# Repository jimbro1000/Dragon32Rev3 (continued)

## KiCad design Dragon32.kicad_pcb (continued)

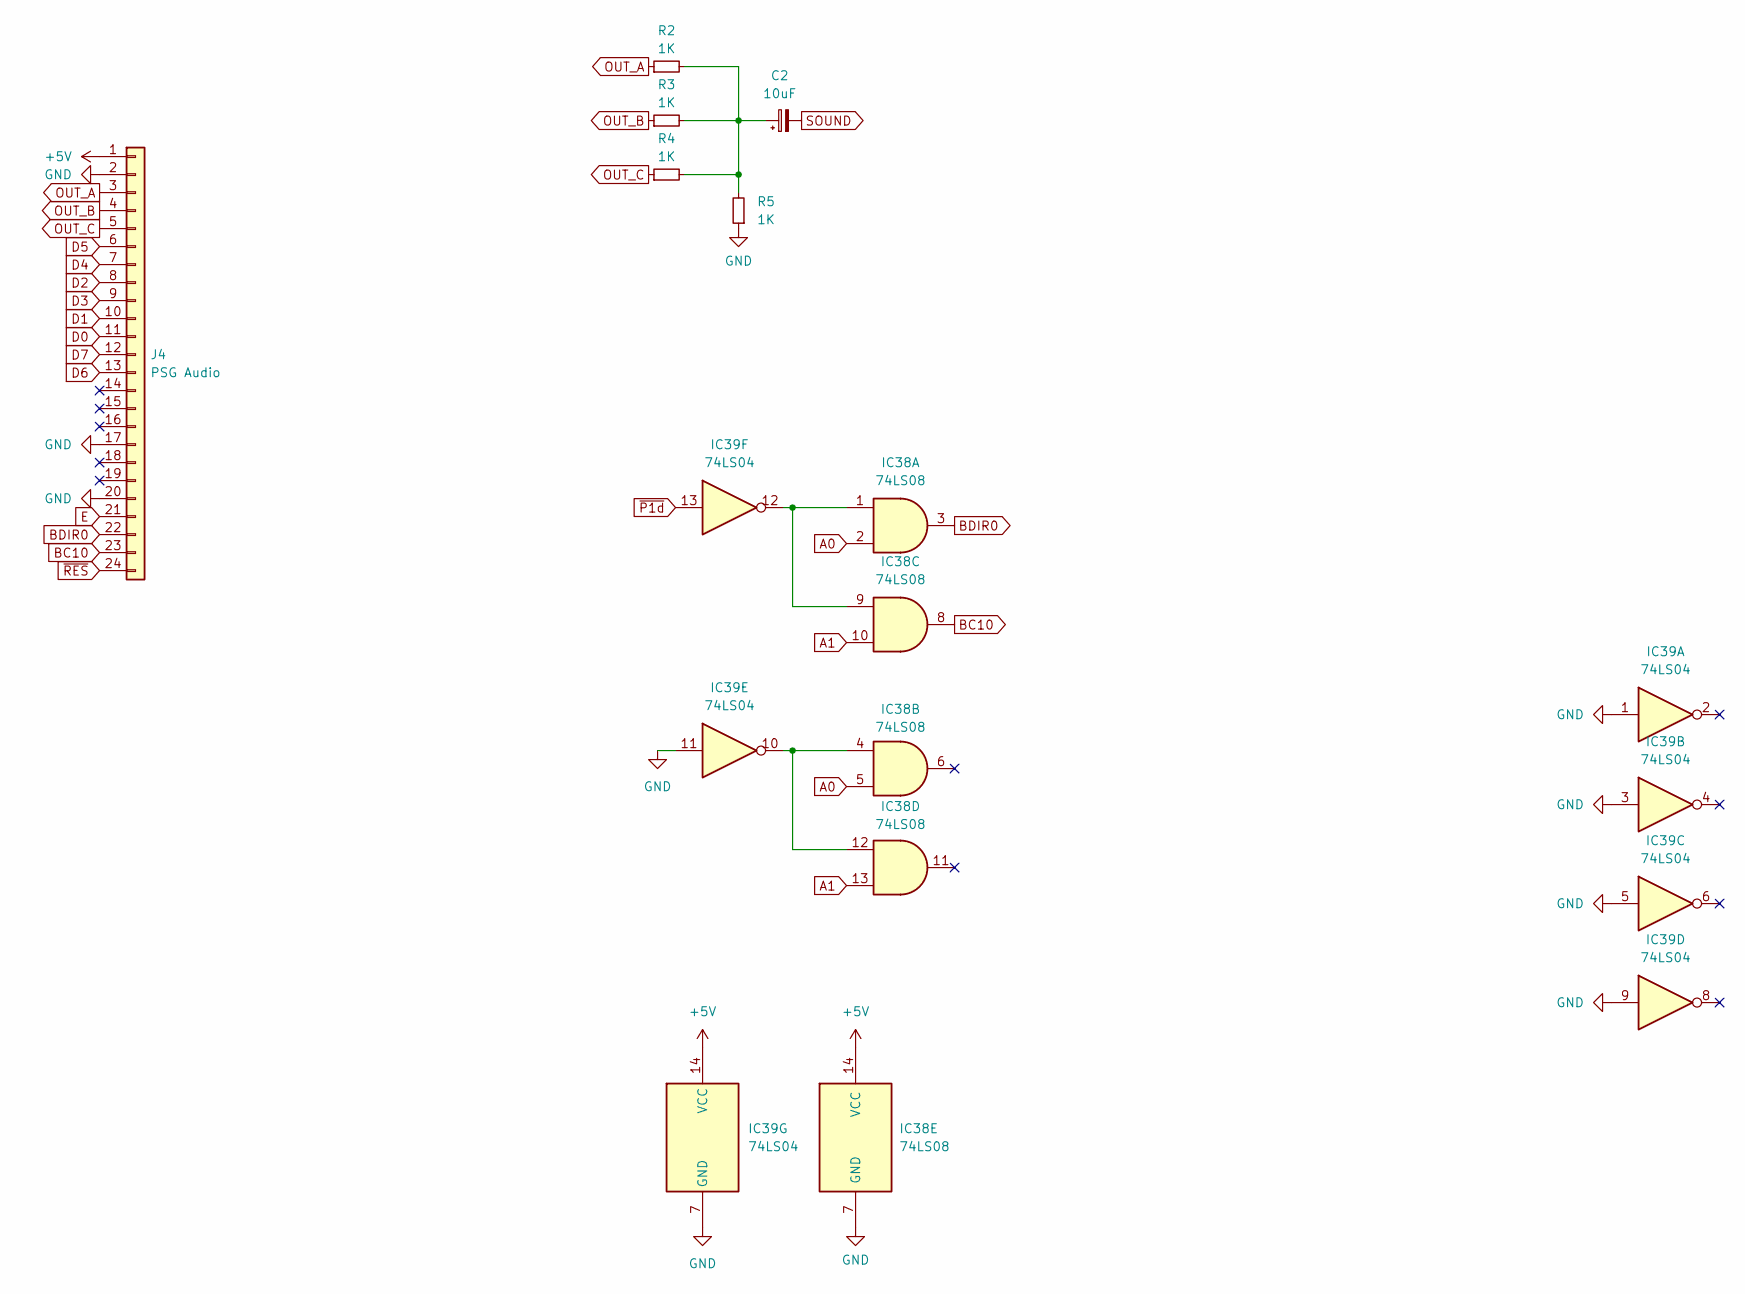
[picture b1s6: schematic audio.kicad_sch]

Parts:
C2: 10uF; CP_Radial_D5.0mm_P2.50mm
IC38: 74LS08; DIP-14_W7.62mm; LCSC C22394768
IC39: 74LS04; DIP-14_W7.62mm; LCSC C22374093
J4: PSG Audio; AY-QTHT
R2, R3, R4: 1K; R_Axial_DIN0207_L6.3mm_D2.5mm_P10.16mm_Horizontal
R5: 1K; R_Axial_DIN0207_L6.3mm_D2.5mm_P2.54mm_Vertical

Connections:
+5V: IC38.14 (VCC), IC39.14 (VCC), J4.1; also elsewhere on the board
A0: IC38.2, IC38.5; also elsewhere on the board
A1: IC38.10, IC38.13; also elsewhere on the board
BC10: IC38.8, J4.23
BDIR0: IC38.3, J4.22
D0: J4.11; also elsewhere on the board
D1: J4.10; also elsewhere on the board
D2: J4.8; also elsewhere on the board
D3: J4.9; also elsewhere on the board
D4: J4.7; also elsewhere on the board
D5: J4.6; also elsewhere on the board
D6: J4.13; also elsewhere on the board
D7: J4.12; also elsewhere on the board
E: J4.21; also elsewhere on the board
unnamed: C2.1, R2.2, R3.2, R4.2, R5.2
unnamed: IC38.1, IC38.9, IC39.12
unnamed: IC38.4, IC38.12, IC39.10
OUT_A: J4.3, R2.1
OUT_B: J4.4, R3.1
OUT_C: J4.5, R4.1
SOUND: C2.2; also elsewhere on the board
~P1d: IC39.13; also elsewhere on the board
~RES: J4.24; also elsewhere on the board

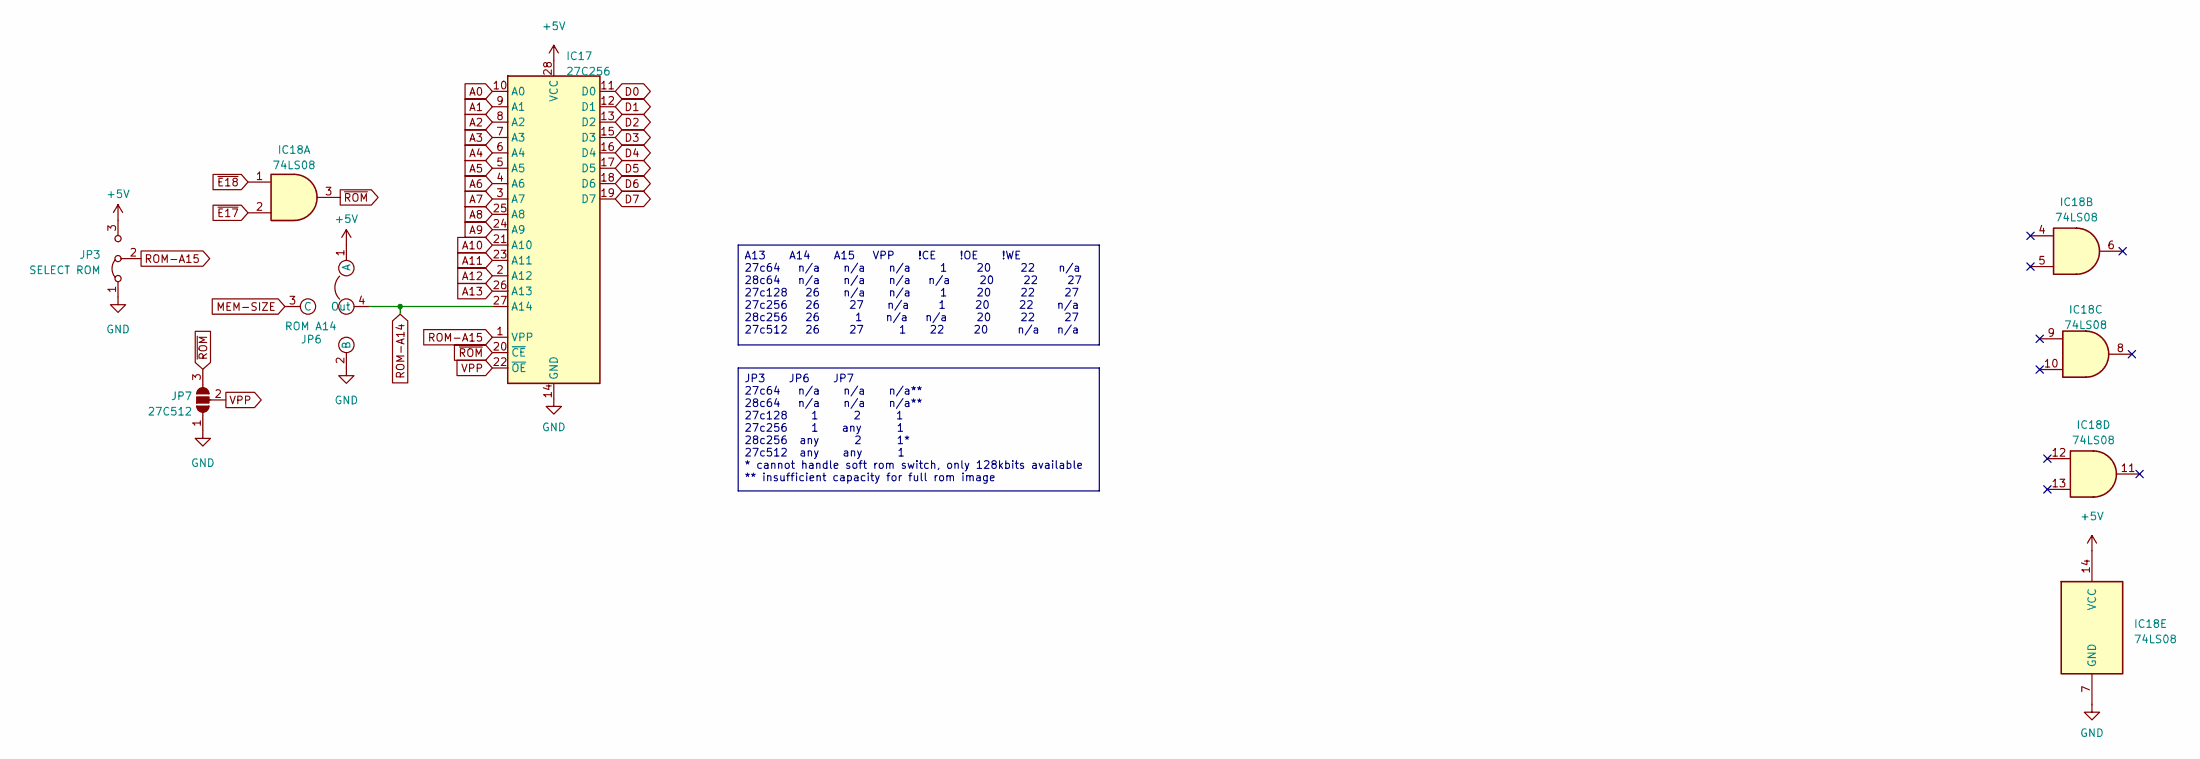
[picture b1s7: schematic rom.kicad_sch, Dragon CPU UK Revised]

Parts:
IC17: 27C256; DIP-28_W15.24mm
IC18: 74LS08; DIP-14_W7.62mm; LCSC C22394768
JP3: SELECT ROM; PinHeader_1x03_P2.54mm_Vertical
JP6: ROM A14; Jumper_4
JP7: 27C512; SolderJumper-3_P1.3mm_Open_Pad1.0x1.5mm

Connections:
+5V: IC17.28 (VCC), IC18.14 (VCC), JP3.3 (B), JP6.1 (A); also elsewhere on the board
A0: IC17.10 (A0); also elsewhere on the board
A1: IC17.9 (A1); also elsewhere on the board
A2: IC17.8 (A2); also elsewhere on the board
A3: IC17.7 (A3); also elsewhere on the board
A4: IC17.6 (A4); also elsewhere on the board
A5: IC17.5 (A5); also elsewhere on the board
A6: IC17.4 (A6); also elsewhere on the board
A7: IC17.3 (A7); also elsewhere on the board
A8: IC17.25 (A8); also elsewhere on the board
A9: IC17.24 (A9); also elsewhere on the board
A10: IC17.21 (A10); also elsewhere on the board
A11: IC17.23 (A11); also elsewhere on the board
A12: IC17.2 (A12); also elsewhere on the board
A13: IC17.26 (A13); also elsewhere on the board
D0: IC17.11 (D0); also elsewhere on the board
D1: IC17.12 (D1); also elsewhere on the board
D2: IC17.13 (D2); also elsewhere on the board
D3: IC17.15 (D3); also elsewhere on the board
D4: IC17.16 (D4); also elsewhere on the board
D5: IC17.17 (D5); also elsewhere on the board
D6: IC17.18 (D6); also elsewhere on the board
D7: IC17.19 (D7); also elsewhere on the board
MEM-SIZE: JP6.3 (C); also elsewhere on the board
ROM-A14: IC17.27 (A14), JP6.4 (Out); also elsewhere on the board
ROM-A15: IC17.1 (VPP), JP3.2 (C); also elsewhere on the board
VPP: IC17.22 (~OE), JP7.2 (C)
~E17: IC18.2; also elsewhere on the board
~E18: IC18.1; also elsewhere on the board
~ROM: IC17.20 (~CE), IC18.3, JP7.3 (B)

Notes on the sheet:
JP3 JP6 JP7 27c64 n/a n/a n/a** 28c64 n/a n/a n/a** 27c128 1 2 1 27c256 1 any 1 28c256 any 2 1* 27c512 any any 1 * cannot handle soft rom switch, only 128kbits available ** insufficient capacity for full rom image
A13 A14 A15 VPP !CE !OE !WE 27c64 n/a n/a n/a 1 20 22 n/a 28c64 n/a n/a n/a n/a 20 22 27 27c128 26 n/a n/a 1 20 22 27 27c256 26 27 n/a 1 20 22 n/a 28c256 26 1 n/a n/a 20 22 27 27c512 26 27 1 22 20 n/a n/a

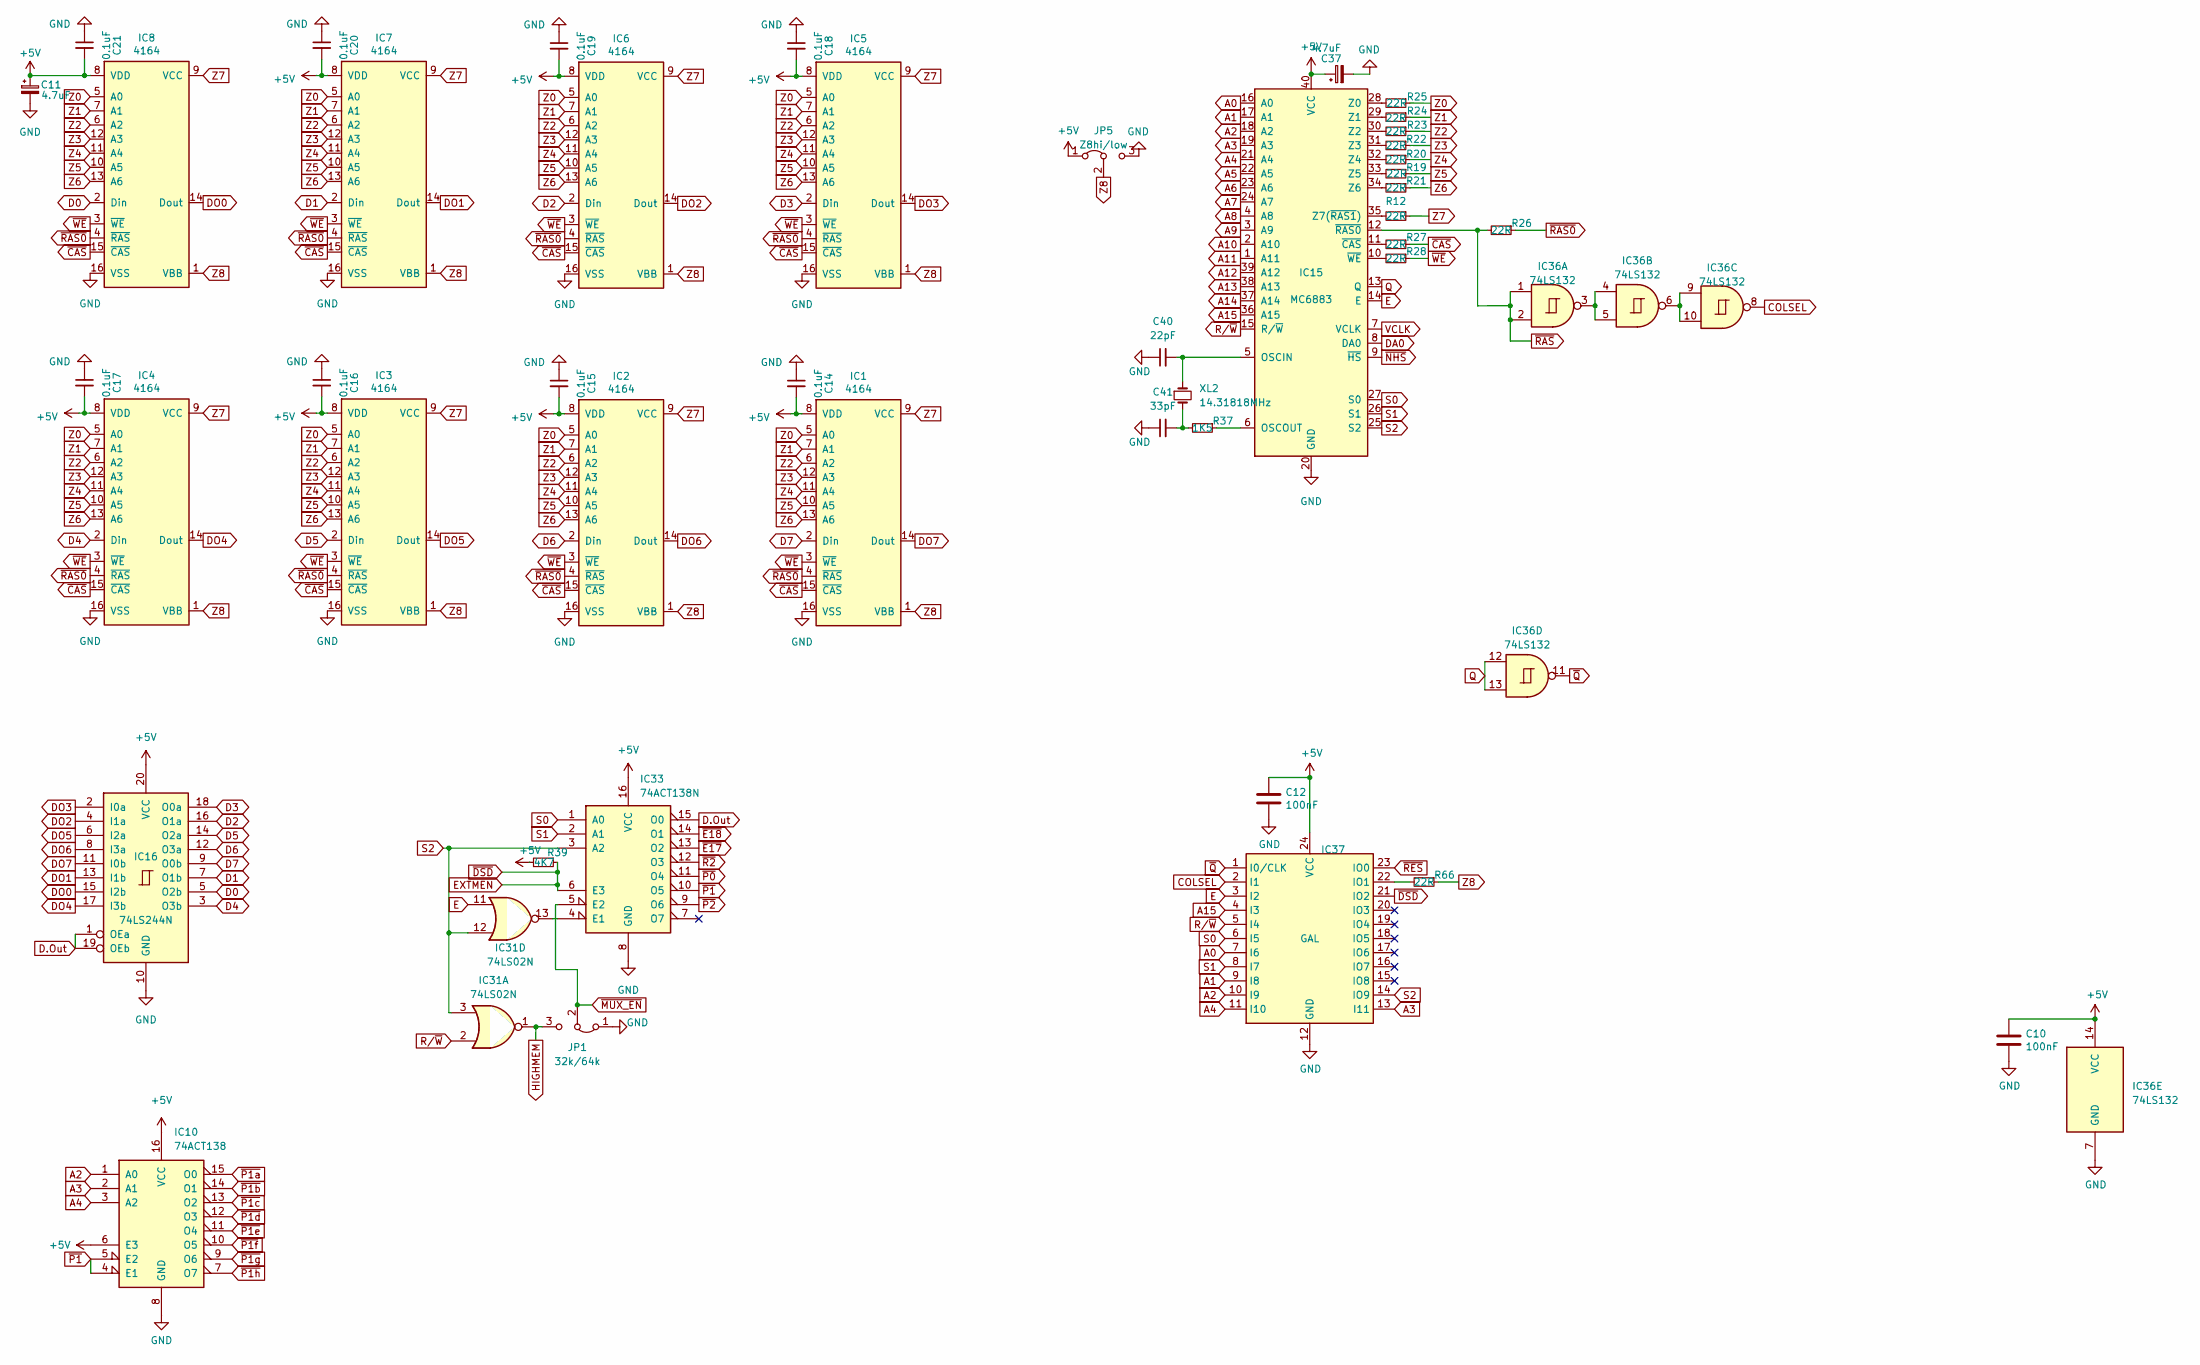
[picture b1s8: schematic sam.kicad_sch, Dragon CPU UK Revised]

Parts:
C10, C12: 100nF; C_0805_2012Metric_Pad1.18x1.45mm_HandSolder; LCSC C1711
C11, C37: 4.7uF; CP_Radial_D5.0mm_P2.50mm; DigiKey 478-8984-1-ND
C14, C15, C16, C17, C18, C19, C20, C21: 0.1uF; C_Disc_D4.3mm_W1.9mm_P5.00mm; DigiKey BC1101CT-ND
C40: 22pF; C_0603_1608Metric_Pad1.08x0.95mm_HandSolder; LCSC C1653
C41: 33pF; C_0603_1608Metric_Pad1.08x0.95mm_HandSolder; LCSC C1663
IC1, IC2, IC3, IC4, IC5, IC6, IC7, IC8: 4164; DIP-16_W7.62mm
IC10: 74ACT138; DIP-16_W7.62mm; LCSC C1547282
IC15: MC6883; DIP-40_W15.24mm
IC16: 74LS244N; DIP-20_W7.62mm; DigiKey 296-1653-5-ND
IC31: 74LS02N; DIP-14_W7.62mm; DigiKey 296-1627-5-ND
IC33: 74ACT138N; DIP-16_W7.62mm; DigiKey 296-1639-5-ND
IC36: 74LS132; DIP-14_W7.62mm
IC37: GAL; DIP-24_W7.62mm
JP1: 32k/64k; PinHeader_1x03_P2.54mm_Vertical
JP5: Z8hi/low; SolderJumper-3_P1.3mm_Open_Pad1.0x1.5mm
R12, R19, R20, R21, R22, R23, R24, R25, R26, R27, R28, R66: 22R; R_0805_2012Metric_Pad1.20x1.40mm_HandSolder; LCSC C17561
R37: 1K5; R_0603_1608Metric_Pad1.05x0.95mm_HandSolder; LCSC C22843
R39: 4K7; R_Axial_DIN0207_L6.3mm_D2.5mm_P2.54mm_Vertical; DigiKey CF14JT4K70CT-ND
XL2: 14.31818MHz; Crystal_HC49-U_Horizontal; DigiKey CTX088-ND

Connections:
+5V: C10.1, C11.1, C12.1, C14.2, C15.2, C16.2, C17.2, C18.2, C19.2, C20.2, C21.2, C37.1, IC1.8 (VDD), IC2.8 (VDD), IC3.8 (VDD), IC4.8 (VDD), IC5.8 (VDD), IC6.8 (VDD), IC7.8 (VDD), IC8.8 (VDD), IC10.6 (E3), IC10.16 (VCC), IC15.40 (VCC), IC16.20 (VCC), IC33.16 (VCC), IC36.14 (VCC), IC37.24 (VCC), JP5.1 (A), R39.2; also elsewhere on the board
A0: IC15.16 (A0), IC37.7 (I6); also elsewhere on the board
A1: IC15.17 (A1), IC37.9 (I8); also elsewhere on the board
A2: IC10.1 (A0), IC15.18 (A2), IC37.10 (I9); also elsewhere on the board
A3: IC10.2 (A1), IC15.19 (A3), IC37.13 (I11); also elsewhere on the board
A4: IC10.3 (A2), IC15.21 (A4), IC37.11 (I10); also elsewhere on the board
A5: IC15.22 (A5); also elsewhere on the board
A6: IC15.23 (A6); also elsewhere on the board
A7: IC15.24 (A7); also elsewhere on the board
A8: IC15.4 (A8); also elsewhere on the board
A9: IC15.3 (A9); also elsewhere on the board
A10: IC15.2 (A10); also elsewhere on the board
A11: IC15.1 (A11); also elsewhere on the board
A12: IC15.39 (A12); also elsewhere on the board
A13: IC15.38 (A13); also elsewhere on the board
A14: IC15.37 (A14); also elsewhere on the board
A15: IC15.36 (A15), IC37.4 (I3); also elsewhere on the board
COLSEL: IC36.8, IC37.2 (I1)
D0: IC8.2 (Din), IC16.5 (O2b); also elsewhere on the board
D1: IC7.2 (Din), IC16.7 (O1b); also elsewhere on the board
D2: IC6.2 (Din), IC16.16 (O1a); also elsewhere on the board
D3: IC5.2 (Din), IC16.18 (O0a); also elsewhere on the board
D4: IC4.2 (Din), IC16.3 (O3b); also elsewhere on the board
D5: IC3.2 (Din), IC16.14 (O2a); also elsewhere on the board
D6: IC2.2 (Din), IC16.12 (O3a); also elsewhere on the board
D7: IC1.2 (Din), IC16.9 (O0b); also elsewhere on the board
D.Out: IC16.1 (OEa), IC16.19 (OEb), IC33.15 (O0)
DA0: IC15.8 (DA0); also elsewhere on the board
DO0: IC8.14 (Dout), IC16.15 (I2b); also elsewhere on the board
DO1: IC7.14 (Dout), IC16.13 (I1b); also elsewhere on the board
DO2: IC6.14 (Dout), IC16.4 (I1a); also elsewhere on the board
DO3: IC5.14 (Dout), IC16.2 (I0a); also elsewhere on the board
DO4: IC4.14 (Dout), IC16.17 (I3b); also elsewhere on the board
DO5: IC3.14 (Dout), IC16.6 (I2a); also elsewhere on the board
DO6: IC2.14 (Dout), IC16.8 (I3a); also elsewhere on the board
DO7: IC1.14 (Dout), IC16.11 (I0b); also elsewhere on the board
E: IC15.14 (E), IC31.11, IC37.3 (I2); also elsewhere on the board
EXTMEN: IC33.6 (E3), IC37.21 (IO2), R39.1; also elsewhere on the board
HIGHMEM: IC31.1, JP1.3 (B); also elsewhere on the board
unnamed: C41.2, R37.2, XL2.2
unnamed: C40.2, IC15.5 (OSCIN), XL2.1
unnamed: IC15.6 (OSCOUT), R37.1
unnamed: IC15.28 (Z0), R25.2
unnamed: IC15.29 (Z1), R24.2
unnamed: IC15.30 (Z2), R23.2
unnamed: IC15.31 (Z3), R22.2
unnamed: IC15.32 (Z4), R20.2
unnamed: IC15.33 (Z5), R19.2
unnamed: IC15.34 (Z6), R21.2
unnamed: IC15.35 (Z7(~RAS1)), R12.2
unnamed: IC15.11 (~CAS), R27.2
unnamed: IC15.10 (~WE), R28.2
unnamed: IC31.13, IC33.4 (E1)
unnamed: IC36.3, IC36.4, IC36.5
unnamed: IC36.6, IC36.9, IC36.10
unnamed: IC37.22 (IO1), R66.2
Q: IC15.13 (Q), IC36.12, IC36.13; also elsewhere on the board
R/~W: IC15.15 (R/~W), IC31.2, IC37.5 (I4); also elsewhere on the board
S0: IC15.27 (S0), IC33.1 (A0), IC37.6 (I5)
S1: IC15.26 (S1), IC33.2 (A1), IC37.8 (I7)
S2: IC15.25 (S2), IC31.3, IC31.12, IC33.3 (A2), IC37.14 (IO9)
VCLK: IC15.7 (VCLK); also elsewhere on the board
Z0: IC1.5 (A0), IC2.5 (A0), IC3.5 (A0), IC4.5 (A0), IC5.5 (A0), IC6.5 (A0), IC7.5 (A0), IC8.5 (A0), R25.1
Z1: IC1.7 (A1), IC2.7 (A1), IC3.7 (A1), IC4.7 (A1), IC5.7 (A1), IC6.7 (A1), IC7.7 (A1), IC8.7 (A1), R24.1
Z2: IC1.6 (A2), IC2.6 (A2), IC3.6 (A2), IC4.6 (A2), IC5.6 (A2), IC6.6 (A2), IC7.6 (A2), IC8.6 (A2), R23.1
Z3: IC1.12 (A3), IC2.12 (A3), IC3.12 (A3), IC4.12 (A3), IC5.12 (A3), IC6.12 (A3), IC7.12 (A3), IC8.12 (A3), R22.1
Z4: IC1.11 (A4), IC2.11 (A4), IC3.11 (A4), IC4.11 (A4), IC5.11 (A4), IC6.11 (A4), IC7.11 (A4), IC8.11 (A4), R20.1
Z5: IC1.10 (A5), IC2.10 (A5), IC3.10 (A5), IC4.10 (A5), IC5.10 (A5), IC6.10 (A5), IC7.10 (A5), IC8.10 (A5), R19.1
Z6: IC1.13 (A6), IC2.13 (A6), IC3.13 (A6), IC4.13 (A6), IC5.13 (A6), IC6.13 (A6), IC7.13 (A6), IC8.13 (A6), R21.1
Z7: IC1.9 (VCC), IC2.9 (VCC), IC3.9 (VCC), IC4.9 (VCC), IC5.9 (VCC), IC6.9 (VCC), IC7.9 (VCC), IC8.9 (VCC), R12.1
Z8: IC1.1 (VBB), IC2.1 (VBB), IC3.1 (VBB), IC4.1 (VBB), IC5.1 (VBB), IC6.1 (VBB), IC7.1 (VBB), IC8.1 (VBB), JP5.2 (C), R66.1
~CAS: IC1.15 (~CAS), IC2.15 (~CAS), IC3.15 (~CAS), IC4.15 (~CAS), IC5.15 (~CAS), IC6.15 (~CAS), IC7.15 (~CAS), IC8.15 (~CAS), R27.1
~E17: IC33.13 (O2); also elsewhere on the board
~E18: IC33.14 (O1); also elsewhere on the board
~MUX_EN: IC33.5 (E2), JP1.2 (C); also elsewhere on the board
~NHS: IC15.9 (~HS); also elsewhere on the board
~P0: IC33.11 (O4); also elsewhere on the board
~P1a: IC10.15 (O0); also elsewhere on the board
~P1b: IC10.14 (O1); also elsewhere on the board
~P1c: IC10.13 (O2); also elsewhere on the board
~P1d: IC10.12 (O3); also elsewhere on the board
~P1e: IC10.11 (O4)
~P1f: IC10.10 (O5)
~P1g: IC10.9 (O6)
~P1h: IC10.7 (O7)
~P1: IC10.4 (E1), IC10.5 (E2), IC33.10 (O5)
~P2: IC33.9 (O6); also elsewhere on the board
~Q: IC36.11, IC37.1 (I0/CLK)
~R2: IC33.12 (O3); also elsewhere on the board
~RAS0: IC1.4 (~RAS), IC2.4 (~RAS), IC3.4 (~RAS), IC4.4 (~RAS), IC5.4 (~RAS), IC6.4 (~RAS), IC7.4 (~RAS), IC8.4 (~RAS), R26.1
~RAS: IC15.12 (~RAS0), IC36.1, IC36.2, R26.2; also elsewhere on the board
~RES: IC37.23 (IO0); also elsewhere on the board
~WE: IC1.3 (~WE), IC2.3 (~WE), IC3.3 (~WE), IC4.3 (~WE), IC5.3 (~WE), IC6.3 (~WE), IC7.3 (~WE), IC8.3 (~WE), R28.1

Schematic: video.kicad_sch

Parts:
J1: Video Output Female; PinSocket_1x05_P2.54mm_Vertical
J2: Board Interconnect Female; PinSocket_2x11_P2.54mm_Vertical
J3: Conn_02x08_Odd_Even; PinSocket_2x08_P2.54mm_Vertical
PL6: Conn_01x09_Male; Molex_KK-396_A-41791-0009_1x09_P3.96mm_Vertical; DigiKey 2057-LHD-09-TS-ND

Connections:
+5V: J1.2, J2.1, PL6.2, PL6.8; also elsewhere on the board
+12V: PL6.1; also elsewhere on the board
-5V: J1.3, PL6.3; also elsewhere on the board
A0: J3.2; also elsewhere on the board
A1: J3.4; also elsewhere on the board
A2: J3.6; also elsewhere on the board
A3: J3.8; also elsewhere on the board
BIAS: J1.1, PL6.9
CSS: J2.19; also elsewhere on the board
D0: J3.1; also elsewhere on the board
D1: J3.3; also elsewhere on the board
D2: J3.5; also elsewhere on the board
D3: J3.7; also elsewhere on the board
D4: J3.9; also elsewhere on the board
D5: J3.11; also elsewhere on the board
D6: J3.13; also elsewhere on the board
D7: J3.15; also elsewhere on the board
DA0: J2.6; also elsewhere on the board
DO0: J2.3; also elsewhere on the board
DO1: J2.5; also elsewhere on the board
DO2: J2.7; also elsewhere on the board
DO3: J2.9; also elsewhere on the board
DO4: J2.11; also elsewhere on the board
DO5: J2.13; also elsewhere on the board
DO6: J2.15; also elsewhere on the board
DO7: J2.17; also elsewhere on the board
E: J3.16; also elsewhere on the board
GM0: J2.14; also elsewhere on the board
GM1: J2.12; also elsewhere on the board
GM2: J2.10; also elsewhere on the board
R/~W: J3.14; also elsewhere on the board
SOUND: PL6.7; also elsewhere on the board
VCLK: J2.18; also elsewhere on the board
VID OUT: J1.4, PL6.6
~A/G: J2.20; also elsewhere on the board
~FS: J2.22; also elsewhere on the board
~NHS: J2.8; also elsewhere on the board
~P1b: J3.12; also elsewhere on the board
~P1c: J3.10; also elsewhere on the board
~RAS: J2.16; also elsewhere on the board
~RES: J2.2; also elsewhere on the board

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
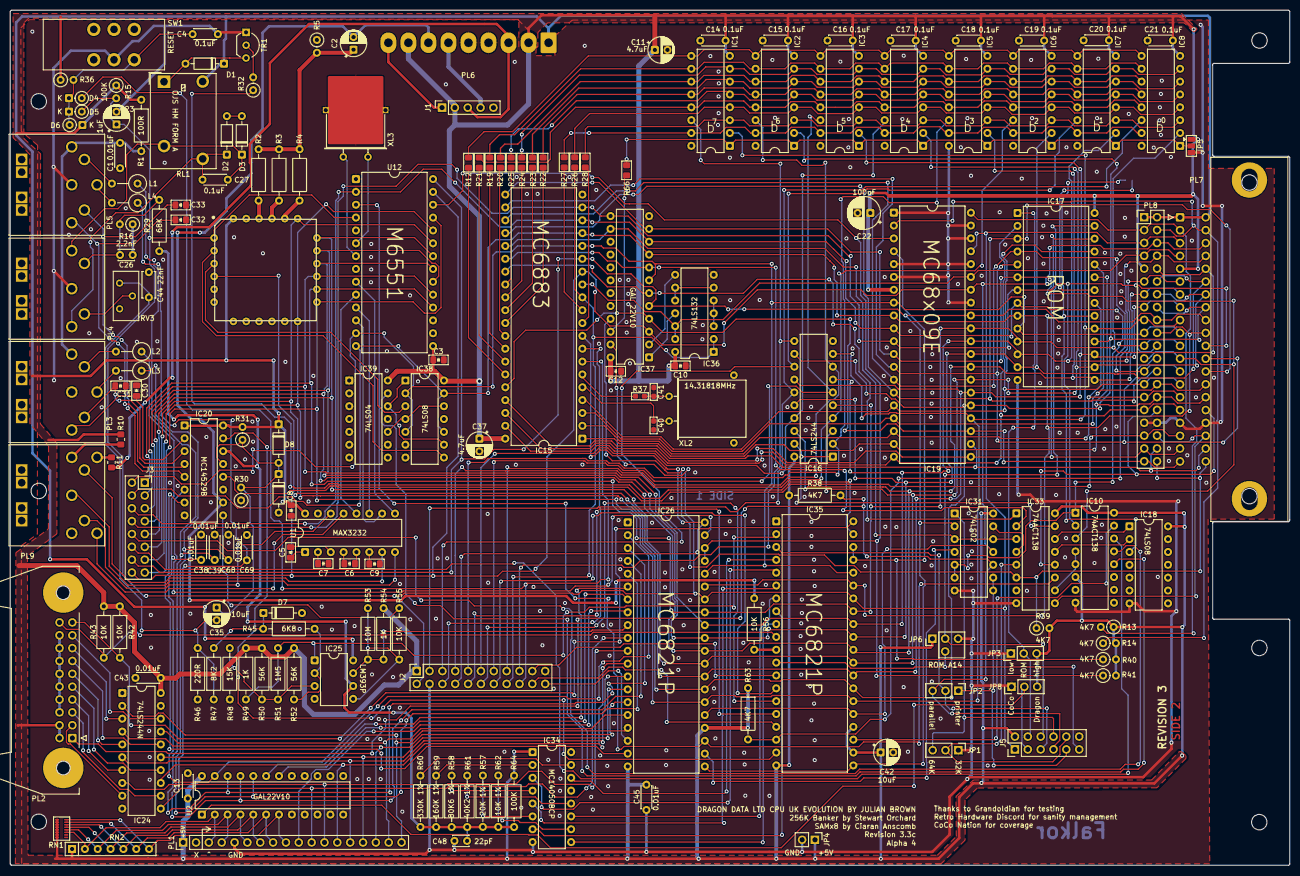
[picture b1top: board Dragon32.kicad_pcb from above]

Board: 2 copper layers, 252.9 x 169.0 mm, 169 parts (1 on the bottom side), 218 nets.

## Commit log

2023-05-29 repack layout
2023-05-29 add 256 banking
2023-05-30 handle 27C512
2023-05-30 include render in readme
2023-06-01 remove video
2023-06-04 add third pia
2023-06-04 add pia2 schematic
2023-08-27 add control for pia 3
2023-08-27 add power pin to keyboard connection
2023-10-02 complete tracing for fabrication
2023-11-13 fix rom and pia select traces
2024-01-14 refresh board for alpha 3
2024-01-14 update render
2024-01-14 add code and jed for gal
2024-03-04 move -5v
2024-03-16 reinforce power rails
2025-01-26 reinforce audio traces
2025-01-26 update readme, tidy up
2025-08-09 migrate to kicad 9
2025-08-10 redo layout for SAMx8
2025-08-10 add uart to board
2025-08-10 align version number
2025-08-11 rework keyboard type selection
2025-08-11 tidy up
2025-08-13 remove redundant renders
2025-08-15 pull up keyboard connections
2025-08-25 refresh BOM
2025-10-05 include CUPL for keyboard GAL
2025-10-05 align versions
2025-10-05 update to keyboard switch option
